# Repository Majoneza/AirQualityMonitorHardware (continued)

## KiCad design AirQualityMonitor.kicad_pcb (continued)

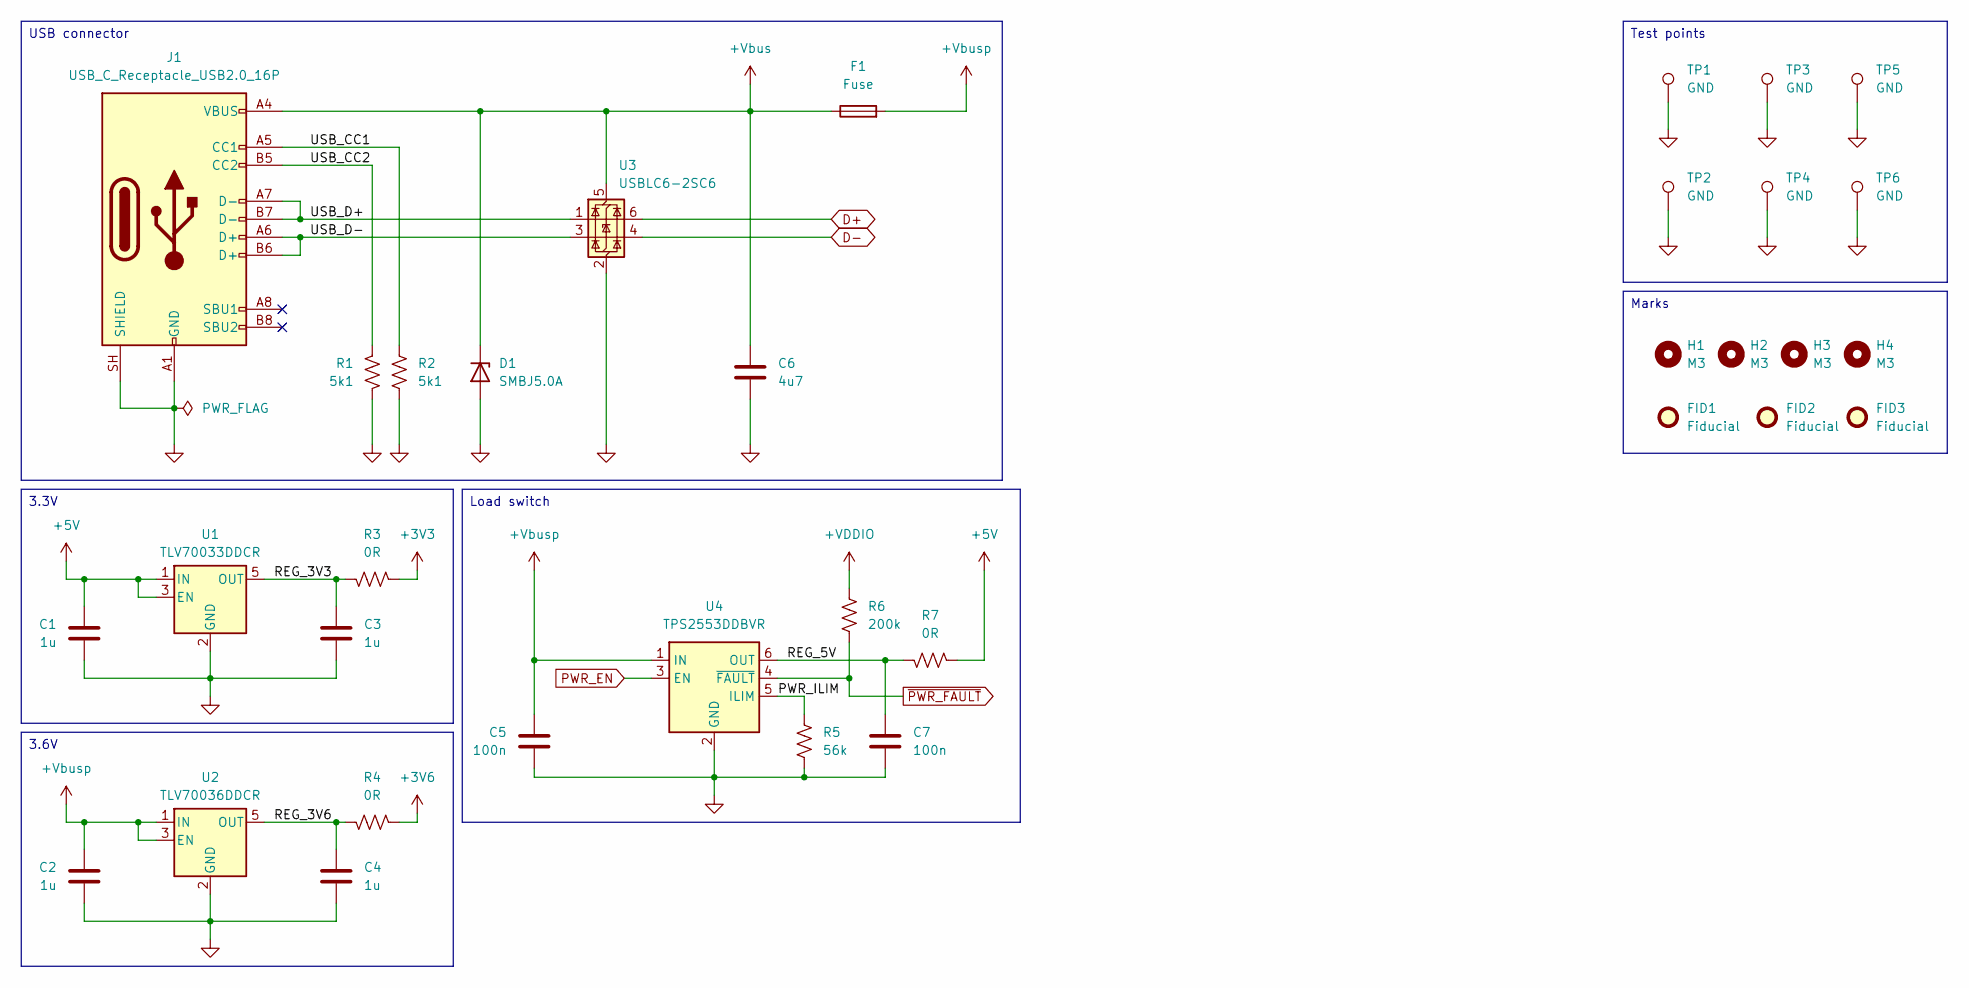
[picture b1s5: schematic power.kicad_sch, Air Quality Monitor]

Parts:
C1, C2, C3, C4: 1u; C_0402_1005Metric; Manufacturer_Part_Number GRM155Z71A105KE01J; Mouser Part Number 81-GRM155Z71A105KE1J
C5, C7: 100n; C_0603_1608Metric; Manufacturer_Part_Number GCJ188R71C104KA01D; Mouser Part Number 81-GCJ188R71C104KA1D
C6: 4u7; C_0603_1608Metric; Manufacturer_Part_Number GRT188C81E475KE13D; Mouser Part Number 81-GRT188C81E475KE3D
D1: SMBJ5.0A; D_SMB; Mouser Part Number 78-SMBJ5.0A
F1: Fuse; Fuse_1206_3216Metric; Manufacturer_Part_Number SF-1206F150-2; Mouser Part Number 652-SF-1206F150-2
FID1, FID2, FID3: Fiducial; Fiducial_1mm_Mask2mm
H1, H2, H3, H4: M3; MountingHole_3mm
J1: USB_C_Receptacle_USB2.0_16P; USB_C_Receptacle_UJ20-C-H-G-SMT-P16-TR; Manufacturer_Part_Number UJ20-C-H-G-SMT-P16-TR; Mouser Part Number 179-UJ20CHGSMTP16TR
R1, R2: 5k1; R_0603_1608Metric; Manufacturer_Part_Number AC0603FR-7W5K1L; Mouser Part Number 603-AC0603FR-7W5K1L
R3, R4, R7: 0R; R_0603_1608Metric; Manufacturer_Part_Number ERJ-S030R00V; Mouser Part Number 667-ERJ-S030R00V
R5: 56k; R_0402_1005Metric; Manufacturer_Part_Number MCS04020C5602FE000; Mouser Part Number 594-MCS04020C5602FE0
R6: 200k; R_0805_2012Metric; Manufacturer_Part_Number AC0805FR-7W200KL; Mouser Part Number 603-AC0805FR-7W200KL
TP1, TP2, TP3, TP4, TP5, TP6: GND; TestPoint_Pad_D1.0mm
U1: TLV70033DDCR; SOT-23-5; Mouser Part Number 595-TLV70033DDCR
U2: TLV70036DDCR; SOT-23-5; Mouser Part Number 595-TLV70036DDCR
U3: USBLC6-2SC6; SOT-23-6; Manufacturer_Part_Number USBLC6-2SC6; Mouser Part Number 511-USBLC6-2SC6
U4: TPS2553DDBVR; SOT-23-6; Mouser Part Number 595-TPS2553DDBVR

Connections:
+3V3: R3.2; also elsewhere on the board
+3V6: R4.2; also elsewhere on the board
+5V: C1.1, R7.2, U1.1 (IN), U1.3 (EN); also elsewhere on the board
+VDDIO: R6.2; also elsewhere on the board
+Vbus: C6.1, D1.1 (K), F1.1, J1.A4 (VBUS), J1.A9 (VBUS), J1.B4 (VBUS), J1.B9 (VBUS), U3.5 (VBUS)
+Vbusp: C2.1, C5.1, F1.2, U2.1 (IN), U2.3 (EN), U4.1 (IN); also elsewhere on the board
/Power/PWR_ILIM: R5.2, U4.5 (ILIM)
/Power/REG_3V3: C3.1, R3.1, U1.5 (OUT)
/Power/REG_3V6: C4.1, R4.1, U2.5 (OUT)
/Power/REG_5V: C7.1, R7.1, U4.6 (OUT)
/Power/USB_CC1: J1.A5 (CC1), R2.1
/Power/USB_CC2: J1.B5 (CC2), R1.1
/Power/USB_D+: J1.A7 (D-), J1.B7 (D-), U3.1 (I/O1)
/Power/USB_D-: J1.A6 (D+), J1.B6 (D+), U3.3 (I/O2)
D+: U3.6 (I/O1); also elsewhere on the board
D-: U3.4 (I/O2); also elsewhere on the board
GND: C1.2, C2.2, C3.2, C4.2, C5.2, C6.2, C7.2, D1.2 (A), J1.A1 (GND), J1.A12 (GND), J1.B1 (GND), J1.B12 (GND), J1.SH (SHIELD), R1.2, R2.2, R5.1, TP1.1 (1_1), TP2.1 (1_1), TP3.1 (1_1), TP4.1 (1_1), TP5.1 (1_1), TP6.1 (1_1), U1.2 (GND), U2.2 (GND), U3.2 (GND), U4.2 (GND); also elsewhere on the board
PWR_EN: U4.3 (EN); also elsewhere on the board
~PWR_FAULT: R6.1, U4.4 (~FAULT); also elsewhere on the board

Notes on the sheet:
Marks
USB connector
Test points
3.6V
Load switch
3.3V

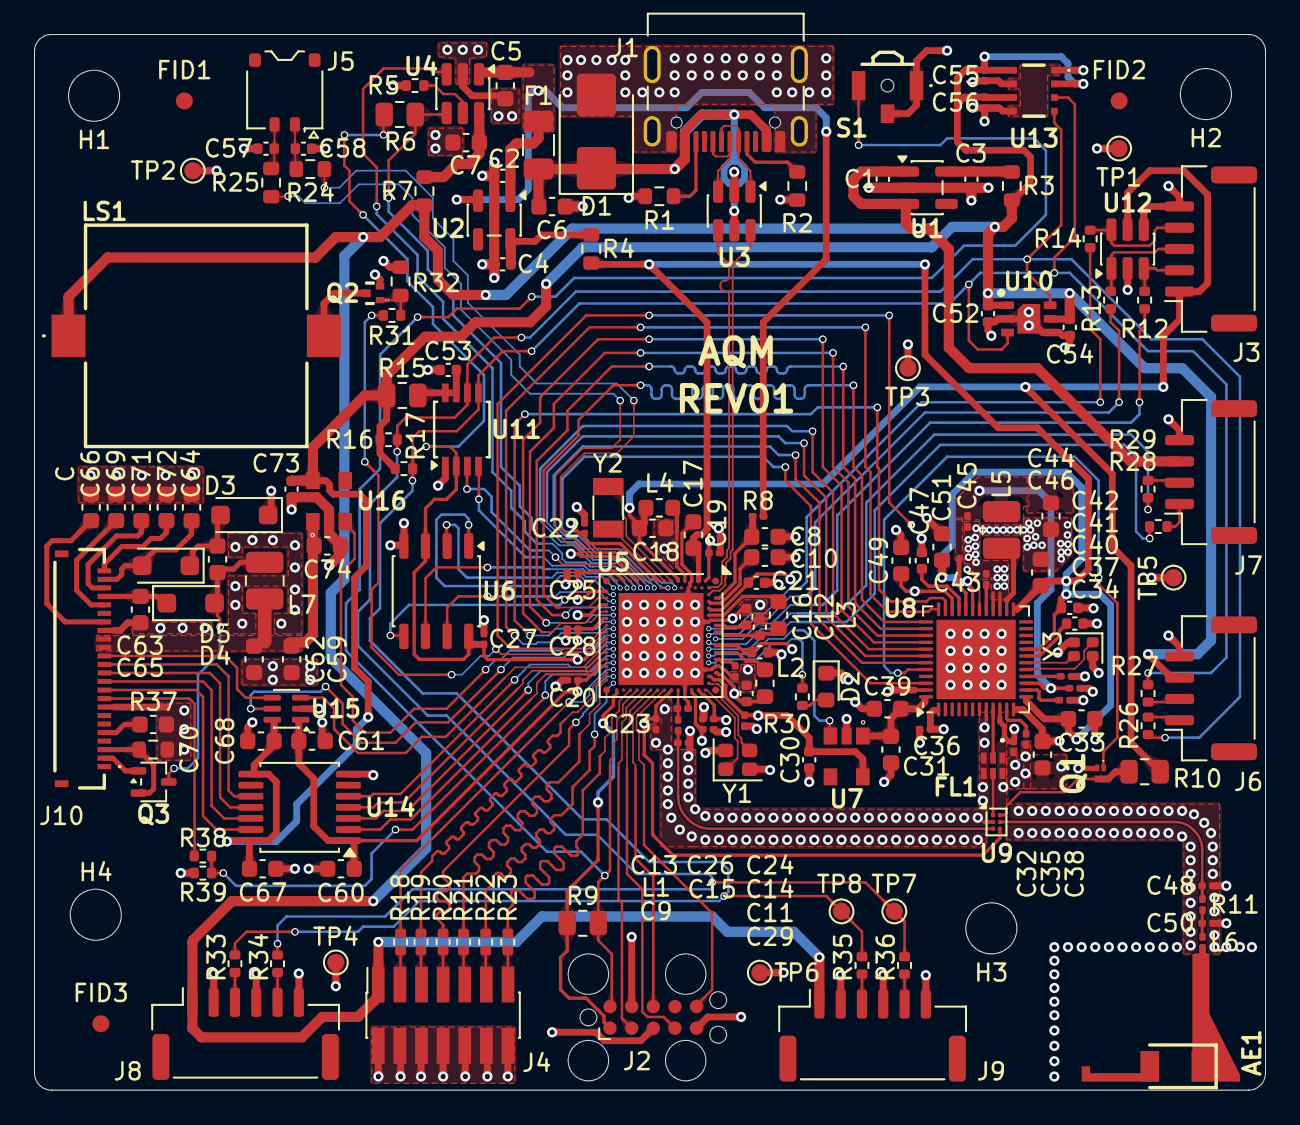
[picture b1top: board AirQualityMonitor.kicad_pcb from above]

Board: 4 copper layers, 72.3 x 62.0 mm, 177 parts (0 on the bottom side), 144 nets.
